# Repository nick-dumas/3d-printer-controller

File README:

This project is a 3D printer controller board.

The goals are (in the following order):
 * Safety (No electrical/fire hazards)
 * Print quality on par with the Duet
 * Modularity on par with ramps
 * Hobbiest level assembly difficulty
 * Cheap

It is intended to be used with a 24v LED strip switching PSU, as well as an external 5v buck-boost regulator.

Currently licensed under:
 Creative Commons Attribution-NonCommercial-ShareAlike 4.0 International License
 http://creativecommons.org/licenses/by-nc-sa/4.0/

This means share-alike, non-commercial.
I plan to release this under a open MIT license once the project is built and complete.
I would also appreciate if you let me know if and how you are using this project.

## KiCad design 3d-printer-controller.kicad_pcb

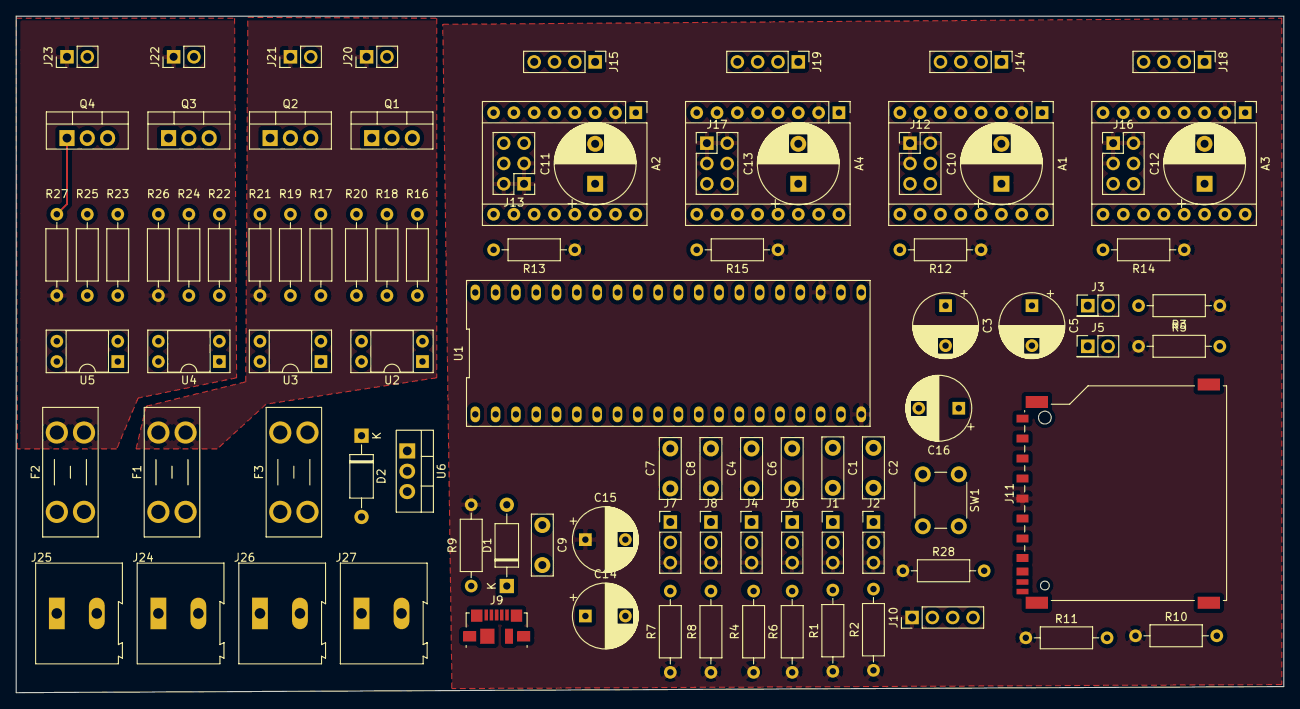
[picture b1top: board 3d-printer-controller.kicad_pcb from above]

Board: 2 copper layers, 158.5 x 84.6 mm, 91 parts (0 on the bottom side), 93 nets.

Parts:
A1, A2, A3, A4: A9488_BREAKOUT; Pololu_Breakout-16_15.2x20.3mm
C1, C2, C4, C6, C7, C8, C9: 1u; C_Disc_D7.5mm_W2.5mm_P5.00mm
C3, C5, C14, C15: 10u; CP_Radial_D8.0mm_P5.00mm
C10, C11, C12, C13: 100u; CP_Radial_D10.0mm_P5.00mm
C16: C; CP_Radial_D8.0mm_P5.00mm
D1, D2: D_Schottky; D_A-405_P10.16mm_Horizontal
F1: FUSE_FAN_1A; Fuseholder_Blade_Mini_Keystone_3568
F2: FUSE_HEAT_15A; Fuseholder_Blade_Mini_Keystone_3568
F3: FUSE_MOT_10A; Fuseholder_Blade_Mini_Keystone_3568
J1: X_MIN; PinHeader_1x03_P2.54mm_Vertical
J2: X_MAX; PinHeader_1x03_P2.54mm_Vertical
J3, J5: THRM0; PinHeader_2x01_P2.54mm_Vertical
J4: Y_MIN; PinHeader_1x03_P2.54mm_Vertical
J6: Y_MAX; PinHeader_1x03_P2.54mm_Vertical
J7: Z_MIN; PinHeader_1x03_P2.54mm_Vertical
J8: Z_MAX; PinHeader_1x03_P2.54mm_Vertical
J9: MICROUSB; USB_Micro-B_Molex_47346-0001
J10: I2C; PinHeader_1x04_P2.54mm_Vertical
J11: SD_Card; SD_TE_2041021
J12: Z_MOT_JMP; PinHeader_2x03_P2.54mm_Vertical
J13: X_MOT_JMP; PinHeader_2x03_P2.54mm_Vertical
J14: Z_MOT; PinHeader_1x04_P2.54mm_Vertical
J15: X_MOT; PinHeader_1x04_P2.54mm_Vertical
J16: E0_MOT_JMP; PinHeader_2x03_P2.54mm_Vertical
J17: Y_MOT_JMP; PinHeader_2x03_P2.54mm_Vertical
J18: E0_MOT; PinHeader_1x04_P2.54mm_Vertical
J19: Y_MOT; PinHeader_1x04_P2.54mm_Vertical
J20: FAN1; PinHeader_1x02_P2.54mm_Vertical
J21: FAN0; PinHeader_1x02_P2.54mm_Vertical
J22: HEAT1; PinHeader_1x02_P2.54mm_Vertical
J23: HEAT0; PinHeader_1x02_P2.54mm_Vertical
J24: FAN_PWR; TerminalBlock_Altech_AK300-2_P5.00mm
J25: HEAT_PWR; TerminalBlock_Altech_AK300-2_P5.00mm
J26: MOT_PWR; TerminalBlock_Altech_AK300-2_P5.00mm
J27: VIN; TerminalBlock_Altech_AK300-2_P5.00mm
Q1, Q2, Q3, Q4: IRFB7546PBF; TO-220-3_Vertical
R1, R2, R4, R6, R7, R8, R12, R13, R14, R15, R28: 10k; R_Axial_DIN0207_L6.3mm_D2.5mm_P10.16mm_Horizontal
R3, R5, R10, R11: 4.7k; R_Axial_DIN0207_L6.3mm_D2.5mm_P10.16mm_Horizontal
R9: 1.5k; R_Axial_DIN0207_L6.3mm_D2.5mm_P10.16mm_Horizontal
R16, R17, R23: 560; R_Axial_DIN0207_L6.3mm_D2.5mm_P10.16mm_Horizontal
R18, R19, R22, R24, R25: 1k; R_Axial_DIN0207_L6.3mm_D2.5mm_P10.16mm_Horizontal
R20, R21, R26, R27: 270; R_Axial_DIN0207_L6.3mm_D2.5mm_P10.16mm_Horizontal
SW1: SW_RST; SW_PUSH_6mm_H5mm
U1: blue_pill; DIP-40_600_ELL
U2, U3, U4, U5: TPC817B_C9G; DIP-4_W7.62mm_Socket
U6: MC33269T-3.3G; TO-220-3_Vertical

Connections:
+3V3: A1.2, A2.2, A3.2, A4.2, C15.1, J1.3, J2.3, J4.3, J6.3, J7.3, J8.3, J10.1, J11.4, J12.1, J12.2, J12.3, J13.1, J13.2, J13.3, J16.1, J16.2, J16.3, J17.1, J17.2, J17.3, R1.1, R2.1, R3.1, R4.1, R5.1, R6.1, R7.1, R8.1, R9.2, R10.1, R11.1, R12.1, R13.1, R14.1, R15.1, R28.1, U1.20, U1.23, U6.3
/EXTR0_DIR: A3.16, U1.14
/EXTR0_EN: A3.9, R14.2, U1.15
/EXTR0_STEP: A3.15, U1.13
/FAN0_PWM: U1.33, U3.1
/FAN1_PWM: U1.34, U2.1
/HEAT0_PWM: U1.35, U5.1
/HEAT1_PWM: U1.36, U4.1
/I2C_SCL: J10.2, R11.2, U1.16
/I2C_SDA: J10.3, R10.2, U1.17
/SPI_MISO: J11.7, U1.30
/SPI_MOSI: J11.2, U1.29
/SPI_NSS0: J11.1, U1.32
/SPI_SCK: J11.5, U1.31
/THRM0: C3.1, J3.2, R3.2, U1.27
/THRM1: C5.1, J5.2, R5.2, U1.28
/USB+: J9.3, R9.1, U1.8
/USB-: J9.2, U1.9
/X_DIR: A2.16, U1.2
/X_EN: A2.9, R13.2, U1.3
/X_MAX: C2.2, J2.2, R2.2, U1.26
/X_MIN: C1.2, J1.2, R1.2, U1.25
/X_STEP: A2.15, U1.1
/Y_DIR: A4.16, U1.5
/Y_EN: A4.9, R15.2, U1.6
/Y_MAX: C6.1, J6.2, R6.2, U1.38
/Y_MIN: C4.1, J4.2, R4.2, U1.37
/Y_STEP: A4.15, U1.4
/Z_DIR: A1.16, U1.11
/Z_EN: A1.9, R12.2, U1.12
/Z_MAX: C8.1, J8.2, R8.2, U1.39
/Z_MIN: C7.1, J7.2, R7.2, U1.7
/Z_STEP: A1.15, U1.10
/~RST: C16.1, R28.2, SW1.1, U1.24
GND: A1.1, A1.7, A2.1, A2.7, A3.1, A3.7, A4.1, A4.7, C1.1, C2.1, C3.2, C4.2, C5.2, C6.2, C7.2, C8.2, C9.1, C10.2, C11.2, C12.2, C13.2, C14.2, C15.2, C16.2, J1.1, J2.1, J3.1, J4.1, J5.1, J6.1, J7.1, J8.1, J9.5, J10.4, J11.3, J11.6, J24.2, J25.2, J26.2, J27.2, Q1.3, Q2.3, Q3.3, Q4.3, R16.2, R17.2, R18.2, R19.2, R22.2, R23.2, R24.2, R25.2, SW1.2, U1.19, U1.21, U1.22, U6.2
unnamed: A1.3, J14.1
unnamed: A1.4, J14.2
unnamed: A1.5, J14.3
unnamed: A1.6, J14.4
unnamed: A1.10, J12.4
unnamed: A1.11, J12.5
unnamed: A1.12, J12.6
unnamed: A1.13, A1.14
unnamed: A2.3, J15.1
unnamed: A2.4, J15.2
unnamed: A2.5, J15.3
unnamed: A2.6, J15.4
unnamed: A2.10, J13.4
unnamed: A2.11, J13.5
unnamed: A2.12, J13.6
unnamed: A2.13, A2.14
unnamed: A3.3, J18.1
unnamed: A3.4, J18.2
unnamed: A3.5, J18.3
unnamed: A3.6, J18.4
unnamed: A3.10, J16.4
unnamed: A3.11, J16.5
unnamed: A3.12, J16.6
unnamed: A3.13, A3.14
unnamed: A4.3, J19.1
unnamed: A4.4, J19.2
unnamed: A4.5, J19.3
unnamed: A4.6, J19.4
unnamed: A4.10, J17.4
unnamed: A4.11, J17.5
unnamed: A4.12, J17.6
unnamed: A4.13, A4.14
unnamed: C9.2, J9.6
unnamed: D1.2, J9.1
unnamed: D2.2, J27.1
unnamed: F1.1, J24.1
unnamed: F2.1, J25.1
unnamed: F3.1, J26.1
unnamed: J20.2, Q1.2
unnamed: J21.2, Q2.2
unnamed: J22.2, Q3.2
unnamed: J23.2, Q4.2
unnamed: Q1.1, R18.1, U2.3
unnamed: Q2.1, R19.1, U3.3
unnamed: Q3.1, R24.1, U4.3
unnamed: Q4.1, R25.1, U5.3
unnamed: R16.1, U2.2
unnamed: R17.1, U3.2
unnamed: R20.1, U2.4
unnamed: R21.1, U3.4
unnamed: R22.1, U4.2
unnamed: R23.1, U5.2
unnamed: R26.1, U4.4
unnamed: R27.1, U5.4
VFAN: F1.2, J20.1, J21.1, R21.2
VHEAT: F2.2, J22.1, J23.1, R20.2, R26.2, R27.2
VIN: C14.1, D1.1, D2.1, U6.1
VMOT: A1.8, A2.8, A3.8, A4.8, C10.1, C11.1, C12.1, C13.1, F3.2

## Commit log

2020-01-02 Schemtic functional v1
    Cleaned up repo and fixed any component/library anomalies.
